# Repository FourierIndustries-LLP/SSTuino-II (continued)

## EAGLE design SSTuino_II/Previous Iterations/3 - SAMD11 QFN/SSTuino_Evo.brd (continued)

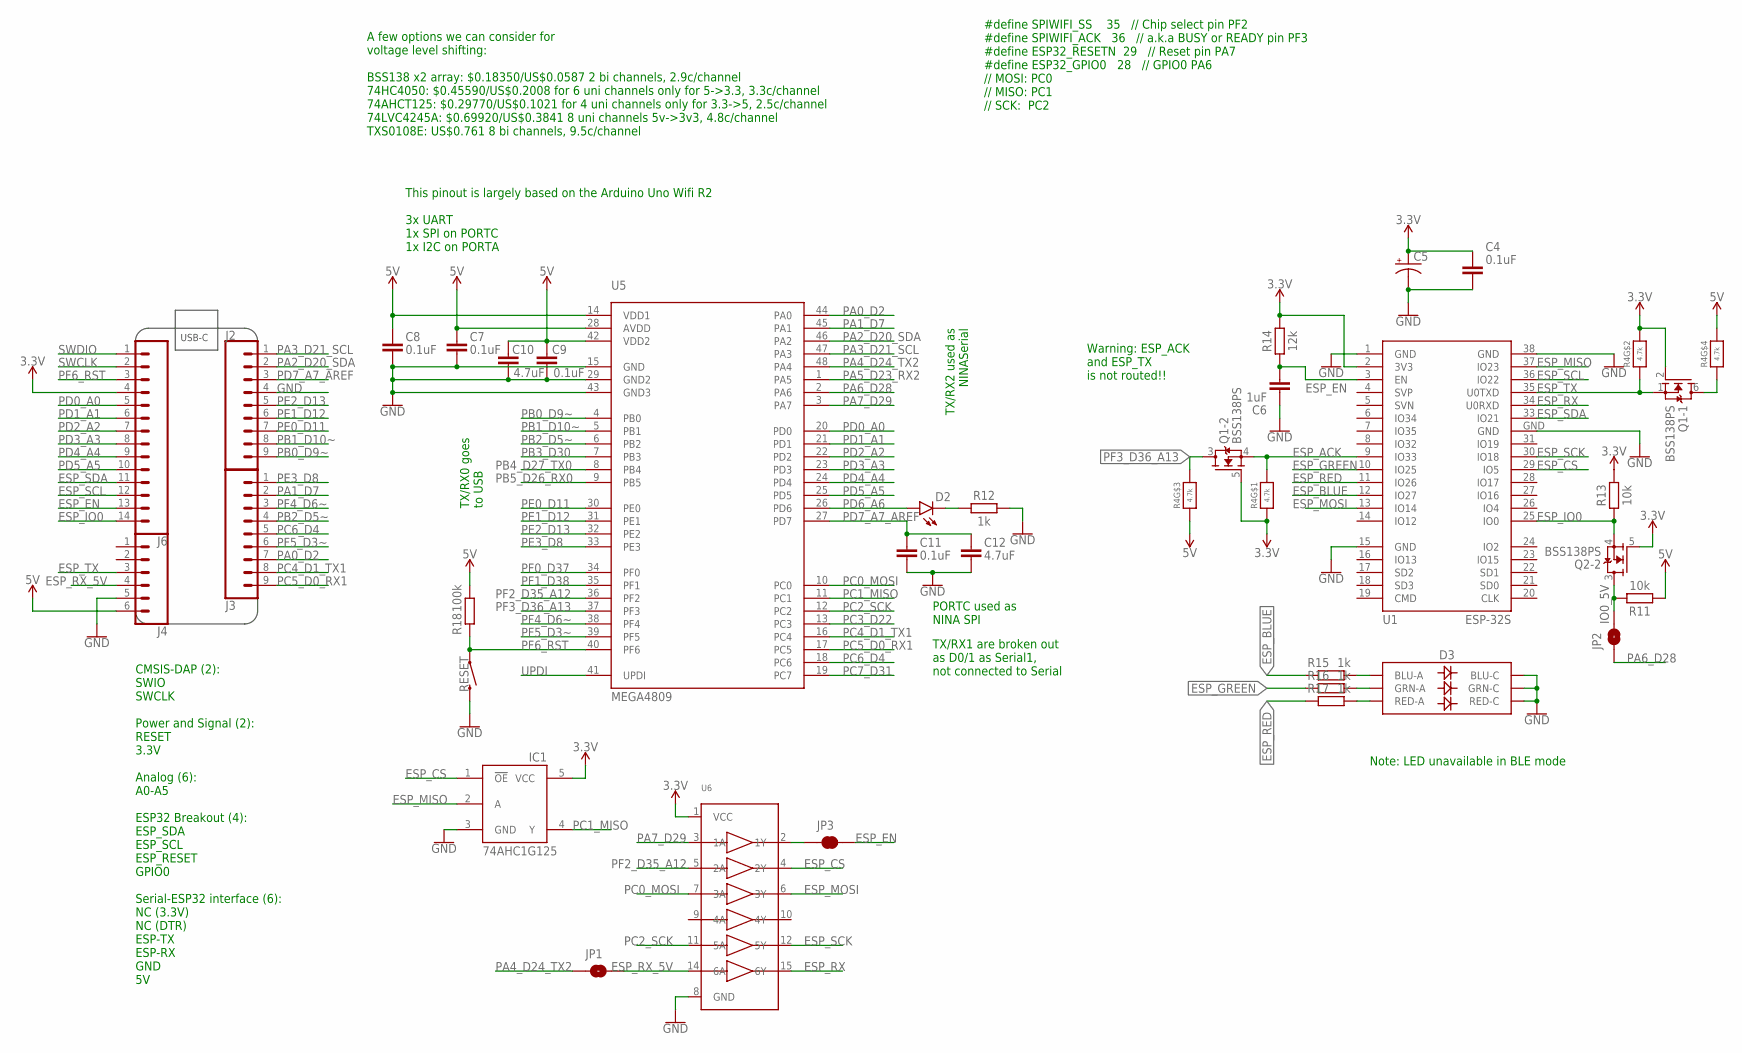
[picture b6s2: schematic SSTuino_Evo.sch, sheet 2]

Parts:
C4, C7, C8, C9, C11: 0.1uF; CAPC1005X60
C5: 100uF; CAPMP3216X180N
C6: 1uF; CAPC1005X60
C10, C12: 4.7uF; CAPC1005X60
D2: LED0603; LED-0603
D3: LED-RGBNO_IC; LED-TRICOLOR-5050; LCSC_PART C784540
IC1: 74AHC1G125; SOT23-5L; LCSC_PART C124295
J2, J3: CONN_09NO_SILK; 1X09_NO_SILK
J4: CONN_06NO_SILK_FEMALE_PTH; 1X06_NO_SILK
J6: CONN_14NO_SILK; 1X14_NO_SILK
JP1, JP2: JUMPER-SMT_2_NO_SILK; SMT-JUMPER_2_NO_SILK
JP3: JUMPER-SMT_2_NC_TRACE_SILK; SMT-JUMPER_2_NC_TRACE_SILK
Q1, Q2: BSS138PS; ARDUINO-TRANSISTORS_SOT363; LCSC_PART C193381
R4: 4.7k; RESPACK_4X0402
R11, R13: 10k; RESC1005X40
R12, R15, R16, R17: 1k; RESC1005X40
R14: 12k; RESC1005X40
R18: 100k; RESC1005X40
RESET: MOMENTARY-SWITCH-SPST-SMD-4.6X2.8MM; TACTILE_SWITCH_SMD_4.6X2.8MM
U1: ESP-32S
U5: MEGA4809; TQFP48; LCSC_PART C189475
U6: 74HC4050DTSSOP; TSSOP16; LCSC_PART C43181

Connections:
3.3V: C4.1, C5.1 (+), IC1.5 (VCC), J6.4, Q1.2 (G), Q1.5 (G), Q2.5 (G), R4.1, R4.7 (2), R13.2, R14.2, U1.2 (3V3), U6.1 (VCC); also elsewhere on the board
5V: C7.1, C8.1, C9.1, C10.1, J4.6, R4.3 (1), R4.5 (2), R11.1, R18.2, U5.14 (VDD1), U5.28 (AVDD), U5.42 (VDD2); also elsewhere on the board
ESP_ACK: Q1.4 (S), R4.8 (2), U1.9 (IO33)
ESP_BLUE: R15.1, U1.12 (IO27)
ESP_CS: IC1.1 (!OE), U1.29 (IO5), U6.4 (2Y)
ESP_EN: C6.2, J6.13, JP3.2, R14.1, U1.3 (EN)
ESP_GREEN: R16.1, U1.10 (IO25)
ESP_IO0: J6.14, Q2.4 (S), R13.1, U1.25 (IO0)
ESP_MISO: IC1.2 (A), U1.37 (IO23)
ESP_MOSI: U1.13 (IO14), U6.6 (3Y)
ESP_RED: R17.1, U1.11 (IO26)
ESP_RX: U1.34 (U0RXD), U6.15 (6Y)
ESP_RX_5V: J4.4, JP1.2, U6.14 (6A)
ESP_SCK: U1.30 (IO18), U6.12 (5Y)
ESP_SCL: J6.12, U1.36 (IO22)
ESP_SDA: J6.11, U1.33 (IO21)
ESP_TX: J4.3, Q1.1 (S), R4.2 (1), U1.35 (U0TXD)
GND: C4.2, C5.2 (-), C6.1, C7.2, C8.2, C9.2, C10.2, C11.2, C12.2, D3.4 (BLU-C), D3.5 (RED-C), D3.6 (GRN-C), IC1.3 (GND), J2.4, J4.5, R12.2, RESET.3 (2), RESET.4 (2), U1.1 (GND), U1.15 (GND), U1.38 (GND), U1.GND, U5.15 (GND), U5.29 (GND2), U5.43 (GND3), U6.8 (GND); also elsewhere on the board
IO0_5V: JP2.2, Q2.3 (D), R11.2
unnamed: Q1.6 (D), R4.4 (1)
unnamed: D2.C, R12.1
unnamed: D3.3 (BLU-A), R15.2
unnamed: JP3.1, U6.2 (1Y)
unnamed: D3.1 (GRN-A), R16.2
unnamed: D3.2 (RED-A), R17.2
PA0_D2: J3.7, U5.44 (PA0)
PA1_D7: J3.2, U5.45 (PA1)
PA2_D20_SDA: J2.2, U5.46 (PA2)
PA3_D21_SCL: J2.1, U5.47 (PA3)
PA4_D24_TX2: JP1.1, U5.48 (PA4)
PA5_D23_RX2: U5.1 (PA5)
PA6_D28: JP2.1, U5.2 (PA6)
PA7_D29: U5.3 (PA7), U6.3 (1A)
PB0_D9~: J2.9, U5.4 (PB0)
PB1_D10~: J2.8, U5.5 (PB1)
PB2_D5~: J3.4, U5.6 (PB2)
PB3_D30: U5.7 (PB3)
PB4_D27_TX0: U5.8 (PB4); also elsewhere on the board
PB5_D26_RX0: U5.9 (PB5); also elsewhere on the board
PC0_MOSI: U5.10 (PC0), U6.7 (3A)
PC1_MISO: IC1.4 (Y), U5.11 (PC1)
PC2_SCK: U5.12 (PC2), U6.11 (5A)
PC3_D22: U5.13 (PC3)
PC4_D1_TX1: J3.8, U5.16 (PC4)
PC5_D0_RX1: J3.9, U5.17 (PC5)
PC6_D4: J3.5, U5.18 (PC6)
PC7_D31: U5.19 (PC7)
PD0_A0: J6.5, U5.20 (PD0)
PD1_A1: J6.6, U5.21 (PD1)
PD2_A2: J6.7, U5.22 (PD2)
PD3_A3: J6.8, U5.23 (PD3)
PD4_A4: J6.9, U5.24 (PD4)
PD5_A5: J6.10, U5.25 (PD5)
PD6_A6: D2.A, U5.26 (PD6)
PD7_A7_AREF: C11.1, C12.1, J2.3, U5.27 (PD7)
PE0_D11: J2.7, U5.30 (PE0)
PE1_D12: J2.6, U5.31 (PE1)
PE2_D13: J2.5, U5.32 (PE2)
PE3_D8: J3.1, U5.33 (PE3)
PF0_D37: U5.34 (PF0)
PF1_D38: U5.35 (PF1)
PF2_D35_A12: U5.36 (PF2), U6.5 (2A)
PF3_D36_A13: Q1.3 (D), R4.6 (2), U5.37 (PF3)
PF4_D6~: J3.3, U5.38 (PF4)
PF5_D3~: J3.6, U5.39 (PF5)
PF6_RST: J6.3, R18.1, RESET.1, RESET.2 (1), U5.40 (PF6)
SWCLK: J6.2; also elsewhere on the board
SWDIO: J6.1; also elsewhere on the board
UPDI: U5.41 (UPDI)

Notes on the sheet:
A few options we can consider for voltage level shifting: BSS138 x2 array: $0.18350/US$0.0587 2 bi channels, 2.9c/channel 74HC4050: $0.45590/US$0.2008 for 6 uni channels only for 5->3.3, 3.3c/channel 74AHCT125: $0.29770/US$0.1021 for 4 uni channels only for 3.3->5, 2.5c/channel 74LVC4245A: $0.69920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
This pinout is largely based on the Arduino Uno Wifi R2 3x UART 1x SPI on PORTC 1x I2C on PORTA
TX/RX2 used as NINASerial
PORTC used as NINA SPI
TX/RX1 are broken out as D0/1 as Serial1, not connected to Serial
TX/RX0 goes to USB
#define SPIWIFI_SS 35 // Chip select pin PF2 #define SPIWIFI_ACK 36 // a.k.a BUSY or READY pin PF3 #define ESP32_RESETN 29 // Reset pin PA7 #define ESP32_GPIO0 28 // GPIO0 PA6 // MOSI: PC0 // MISO: PC1 // SCK: PC2
Note: LED unavailable in BLE mode
USB-C
CMSIS-DAP (2): SWIO SWCLK Power and Signal (2): RESET 3.3V Analog (6): A0-A5 ESP32 Breakout (4): ESP_SDA ESP_SCL ESP_RESET GPIO0 Serial-ESP32 interface (6): NC (3.3V) NC (DTR) ESP-TX ESP-RX GND 5V
Warning: ESP_ACK and ESP_TX is not routed!!

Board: 2 copper layers, 49 parts (3 on the bottom side), 72 nets, no tracks yet.

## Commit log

2021-10-19 reorganised folder
2021-10-19 better folder structure
2021-10-20 updated some docs
2021-10-21 updated EVT procedures
2021-11-29 added jig
2021-11-29 updated documentation
2021-11-29 added license and readme
2021-12-24 Added Explorer board
2021-12-24 improved details regarding testing
2021-12-24 finalised test jig
2021-12-24 added JST SH connector for SPI
2022-01-16 finalised SSTuino II main board
2022-01-16 updated explorer board
2022-01-16 final version of the revA jig, revB incoming soon
2022-02-18 updated QC testing procedures
2022-02-18 updated test jig
2022-02-18 updated Explorer board to first prototype version
2022-02-27 completed modifications to Explorer board for final production
2022-06-07 added pinout diagram
2022-07-03 updated BOM for 2022/23 batch
2022-12-29 added gerber and necessary production files
2023-07-23 added PDF of schematic
2024-05-03 added auto tool
2024-05-03 added dmg check in autorepair script
2025-04-01 Update sstuino-autorepair.sh
    Updated autorepair script to new core name
